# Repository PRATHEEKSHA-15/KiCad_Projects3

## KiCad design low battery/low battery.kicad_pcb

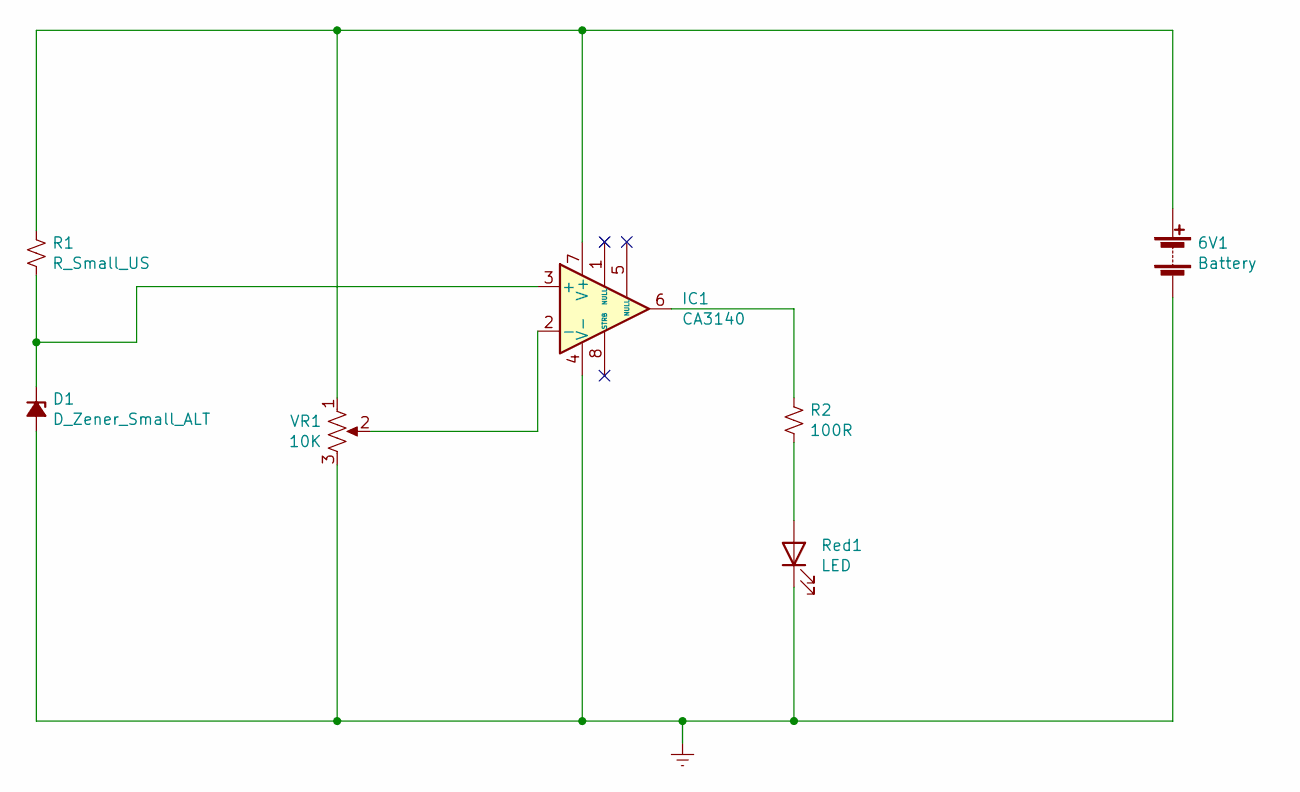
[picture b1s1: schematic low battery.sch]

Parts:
6V1: Battery; PinSocket_1x02_P2.54mm_Vertical
D1: D_Zener_Small_ALT; D_DO-201AE_P5.08mm_Vertical_AnodeUp
IC1: CA3140; DIP-8_W7.62mm_LongPads
R1: R_Small_US; R_Axial_DIN0204_L3.6mm_D1.6mm_P5.08mm_Horizontal
R2: 100R; R_Axial_DIN0204_L3.6mm_D1.6mm_P5.08mm_Horizontal
Red1: LED; LED_D3.0mm
VR1: 10K; Potentiometer_Alps_RK09Y11_Single_Horizontal

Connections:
Earth: 6V1.2 (-), D1.2 (A), IC1.4 (V-), Red1.1 (K), VR1.3
unnamed: 6V1.1 (+), IC1.7 (V+), R1.1, VR1.1
unnamed: D1.1 (K), IC1.3 (+), R1.2
unnamed: IC1.2 (-), VR1.2
unnamed: IC1.6, R2.1
unnamed: R2.2, Red1.2 (A)

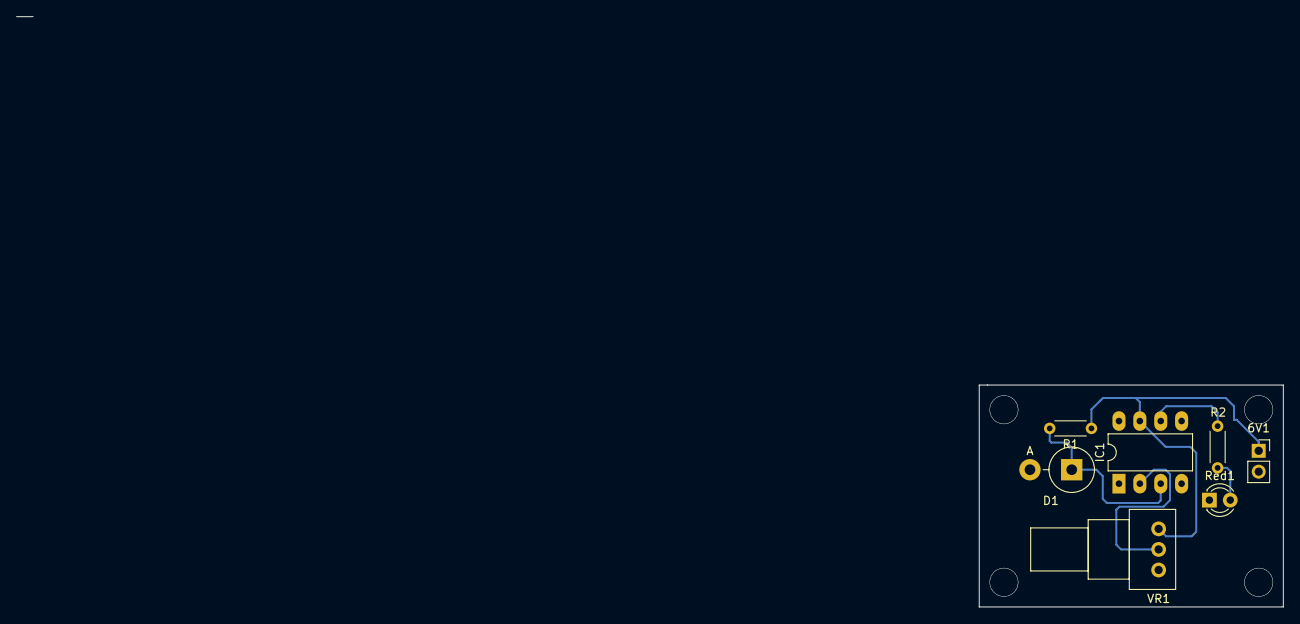
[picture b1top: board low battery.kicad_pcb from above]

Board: 2 copper layers, 37.0 x 27.0 mm, 7 parts (0 on the bottom side), 6 nets.

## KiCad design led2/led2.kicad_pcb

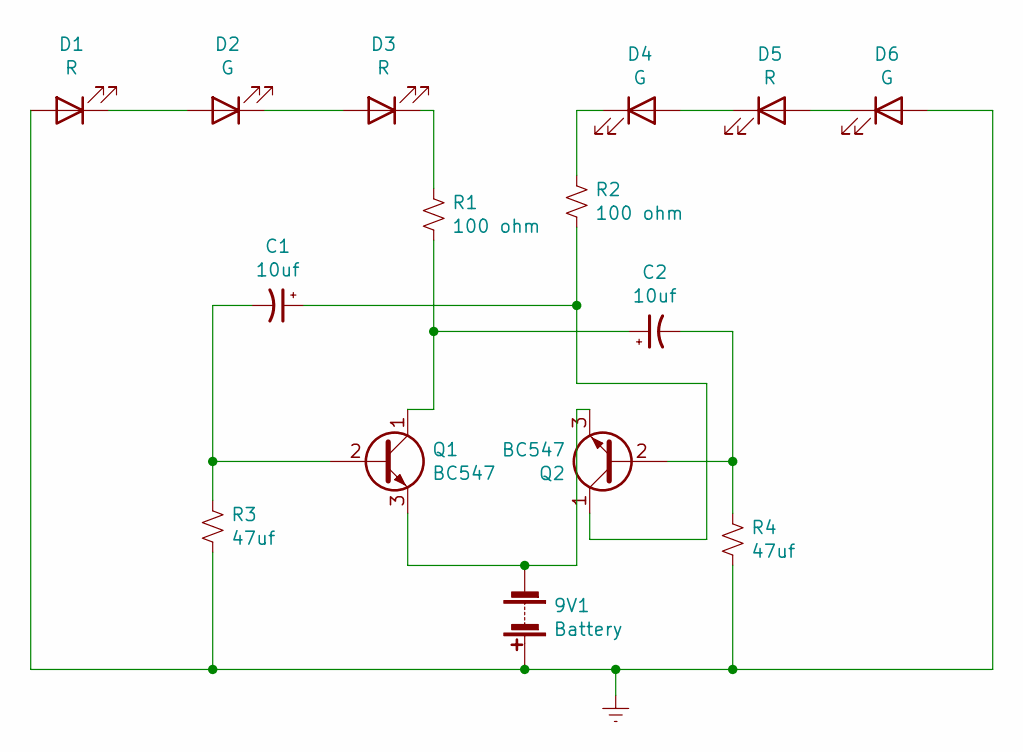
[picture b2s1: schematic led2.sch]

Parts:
9V1: Battery; PinSocket_1x02_P2.54mm_Vertical
C1, C2: 10uf; CP_Radial_D4.0mm_P2.00mm
D1, D3, D5: R; LED_D3.0mm
D2, D4, D6: G; LED_D3.0mm
Q1, Q2: BC547; TO-92_Inline
R1, R2: 100 ohm; R_Axial_DIN0204_L3.6mm_D1.6mm_P5.08mm_Horizontal
R3, R4: 47uf; R_Axial_DIN0204_L3.6mm_D1.6mm_P5.08mm_Horizontal

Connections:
Earth: 9V1.1 (+), D1.2 (A), D6.2 (A), R3.2, R4.2
unnamed: 9V1.2 (-), Q1.3 (E), Q2.3 (E)
unnamed: C1.1, Q2.1 (C), R2.2
unnamed: C1.2, Q1.2 (B), R3.1
unnamed: C2.1, Q1.1 (C), R1.2
unnamed: C2.2, Q2.2 (B), R4.1
unnamed: D1.1 (K), D2.2 (A)
unnamed: D2.1 (K), D3.2 (A)
unnamed: D3.1 (K), R1.1
unnamed: D4.1 (K), R2.1
unnamed: D4.2 (A), D5.1 (K)
unnamed: D5.2 (A), D6.1 (K)

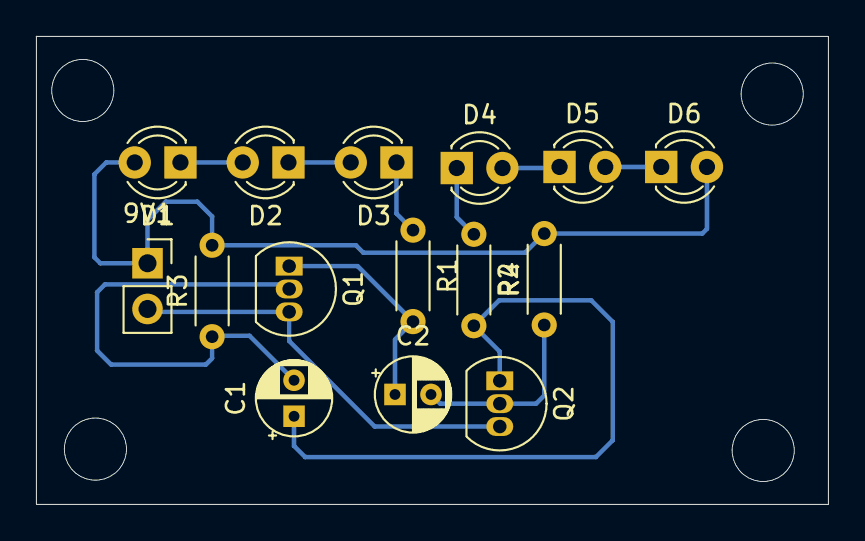
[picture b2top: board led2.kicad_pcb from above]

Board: 2 copper layers, 44.0 x 26.0 mm, 15 parts (0 on the bottom side), 12 nets.

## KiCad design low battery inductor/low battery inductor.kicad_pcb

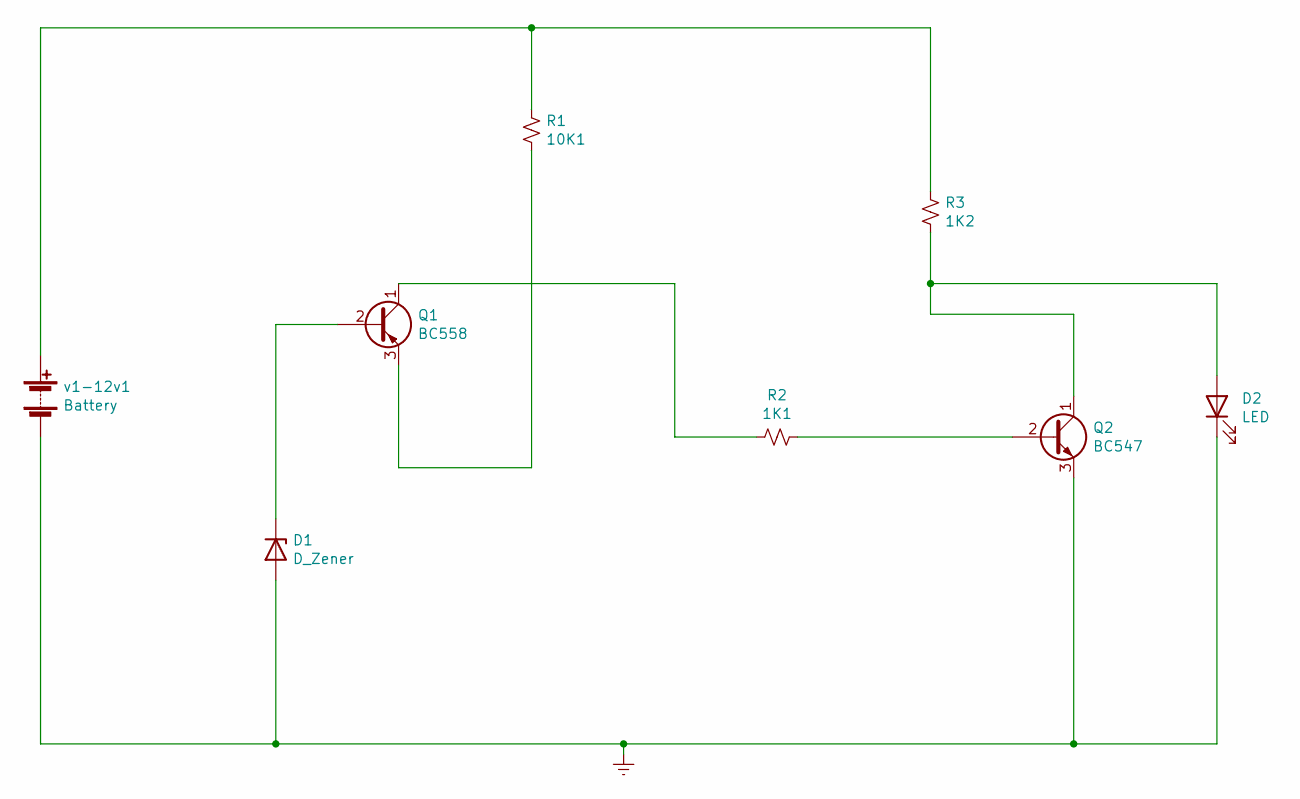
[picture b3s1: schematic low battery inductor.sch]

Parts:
D1: D_Zener; D_DO-35_SOD27_P2.54mm_Vertical_AnodeUp
D2: LED; LED_D3.0mm
Q1: BC558; TO-92_Inline
Q2: BC547; TO-92_Inline
R1: 10K1; R_Axial_DIN0204_L3.6mm_D1.6mm_P5.08mm_Horizontal
R2: 1K1; R_Axial_DIN0204_L3.6mm_D1.6mm_P5.08mm_Horizontal
R3: 1K2; R_Axial_DIN0204_L3.6mm_D1.6mm_P5.08mm_Horizontal
v1-12v1: Battery; PinSocket_1x02_P2.54mm_Vertical

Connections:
Earth: D1.2 (A), D2.1 (K), Q2.3 (E), v1-12v1.2 (-)
unnamed: D1.1 (K), Q1.2 (B)
unnamed: D2.2 (A), Q2.1 (C), R3.2
unnamed: Q1.1 (C), R2.1
unnamed: Q1.3 (E), R1.2
unnamed: Q2.2 (B), R2.2
unnamed: R1.1, R3.1, v1-12v1.1 (+)

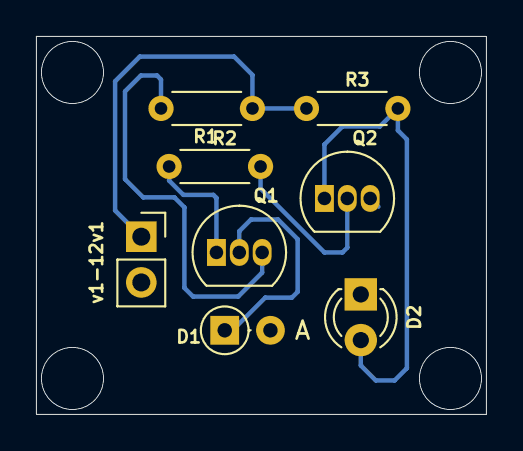
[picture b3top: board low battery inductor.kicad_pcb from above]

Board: 2 copper layers, 25.0 x 21.0 mm, 8 parts (0 on the bottom side), 7 nets.
